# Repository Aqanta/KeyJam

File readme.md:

# Aqanta KeyJam

The Aqanta KeyJam is a powerful opensource macro-pad that can be configured to send HID keystrokes, run complex macros on a connected computer, or be used as a drum-pad. 
The KeyJam runs on an RP2040 (Pico) board and can use a companion Electron app for control.

All code, designs, and methodology can be found in this repo. The project is unfinished and will be updated over time.

## Drums on Alpine Linux

APK installs:

fluidsynth

fluidsynth python driver is here, needs to be installed manually

https://github.com/nwhitehead/pyfluidsynth

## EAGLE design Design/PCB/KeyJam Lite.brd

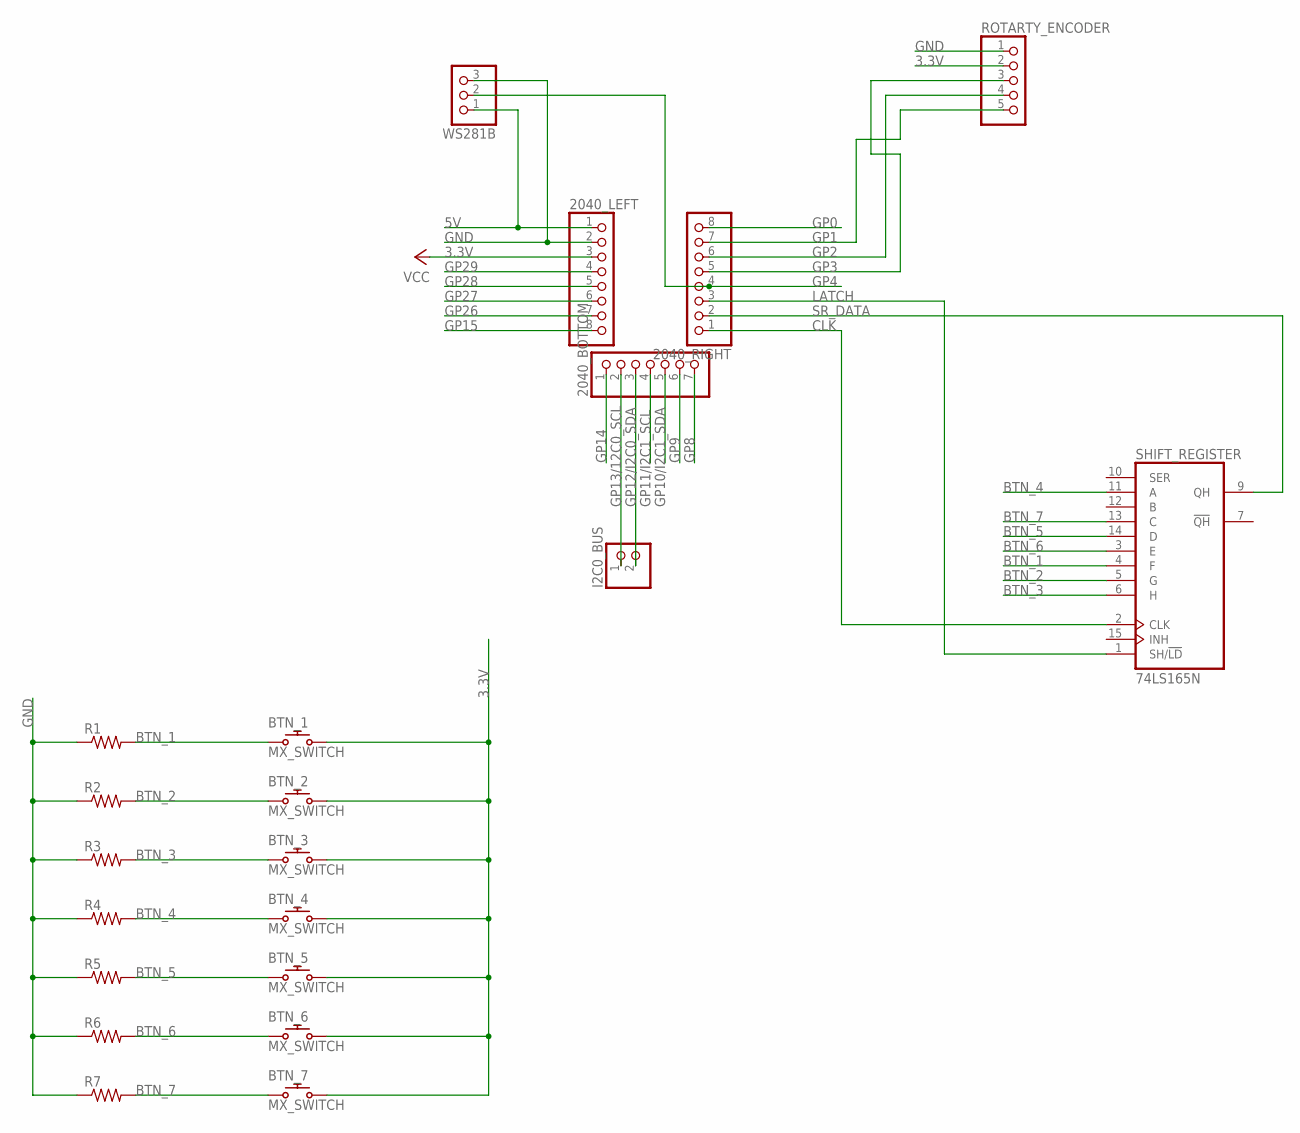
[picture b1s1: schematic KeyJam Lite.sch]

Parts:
2040_BOTTOM: PINHD-1X7; 1X07
2040_LEFT, 2040_RIGHT: PINHD-1X8; 1X08
BTN_1, BTN_2, BTN_3, BTN_4, BTN_5, BTN_6, BTN_7: MX_SWITCH
I2C0_BUS: PINHD-1X2; 1X02
R1, R2, R3, R4, R5, R6, R7: ADAFRUIT_R-US_R0805; ADAFRUIT_R0805
ROTARTY_ENCODER: PINHD-1X5; 1X05
SHIFT_REGISTER: 74LS165N; DIL16
WS281B: PINHD-1X3; 1X03

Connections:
3.3V: 2040_LEFT.3, BTN_1.S2 (2), BTN_2.S2 (2), BTN_3.S2 (2), BTN_4.S2 (2), BTN_5.S2 (2), BTN_6.S2 (2), BTN_7.S2 (2), ROTARTY_ENCODER.2, SHIFT_REGISTER.16 (VCC)
5V: 2040_LEFT.1, WS281B.1
BTN_1: BTN_1.S1 (1), R1.2, SHIFT_REGISTER.4 (F)
BTN_2: BTN_2.S1 (1), R2.2, SHIFT_REGISTER.5 (G)
BTN_3: BTN_3.S1 (1), R3.2, SHIFT_REGISTER.6 (H)
BTN_4: BTN_4.S1 (1), R4.2, SHIFT_REGISTER.11 (A)
BTN_5: BTN_5.S1 (1), R5.2, SHIFT_REGISTER.14 (D)
BTN_6: BTN_6.S1 (1), R6.2, SHIFT_REGISTER.3 (E)
BTN_7: BTN_7.S1 (1), R7.2, SHIFT_REGISTER.13 (C)
CLK: 2040_RIGHT.1, SHIFT_REGISTER.2 (CLK)
GND: 2040_LEFT.2, R1.1, R2.1, R3.1, R4.1, R5.1, R6.1, R7.1, ROTARTY_ENCODER.1, SHIFT_REGISTER.8 (GND), WS281B.3
GP0: 2040_RIGHT.8
GP1: 2040_RIGHT.7, ROTARTY_ENCODER.5
GP2: 2040_RIGHT.6, ROTARTY_ENCODER.4
GP3: 2040_RIGHT.5, ROTARTY_ENCODER.3
GP4: 2040_RIGHT.4, WS281B.2
GP8: 2040_BOTTOM.7
GP9: 2040_BOTTOM.6
GP10/I2C1_SDA: 2040_BOTTOM.5
GP11/I2C1_SCL: 2040_BOTTOM.4
GP12/I2C0_SDA: 2040_BOTTOM.3, I2C0_BUS.2
GP13/12C0_SCL: 2040_BOTTOM.2, I2C0_BUS.1
GP14: 2040_BOTTOM.1
GP15: 2040_LEFT.8
GP26: 2040_LEFT.7
GP27: 2040_LEFT.6
GP28: 2040_LEFT.5
GP29: 2040_LEFT.4
LATCH: 2040_RIGHT.3, SHIFT_REGISTER.1 (SH/!LD)
SR_DATA: 2040_RIGHT.2, SHIFT_REGISTER.9 (QH)

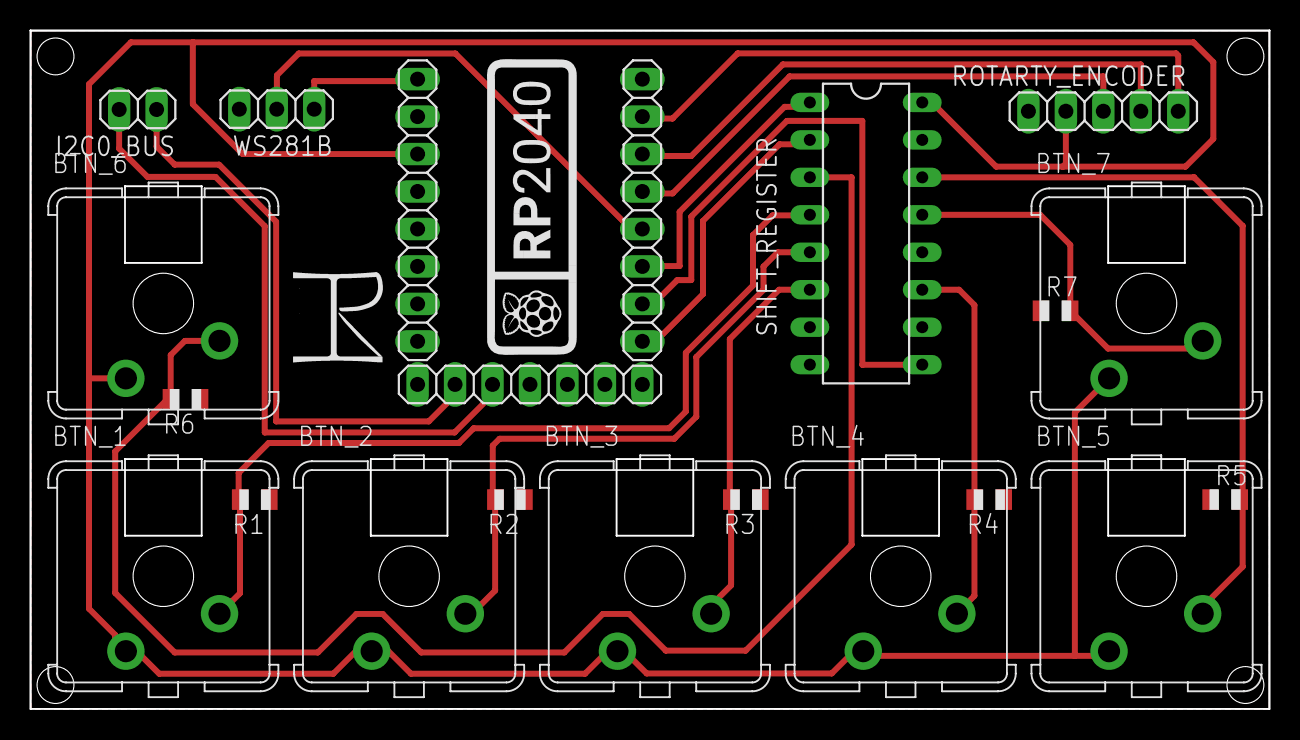
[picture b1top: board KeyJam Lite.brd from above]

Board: 2 copper layers, 84.0 x 46.0 mm, 22 parts (0 on the bottom side), 19 nets.

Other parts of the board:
U$1: RASPI_RP2040_LOGO_20MM

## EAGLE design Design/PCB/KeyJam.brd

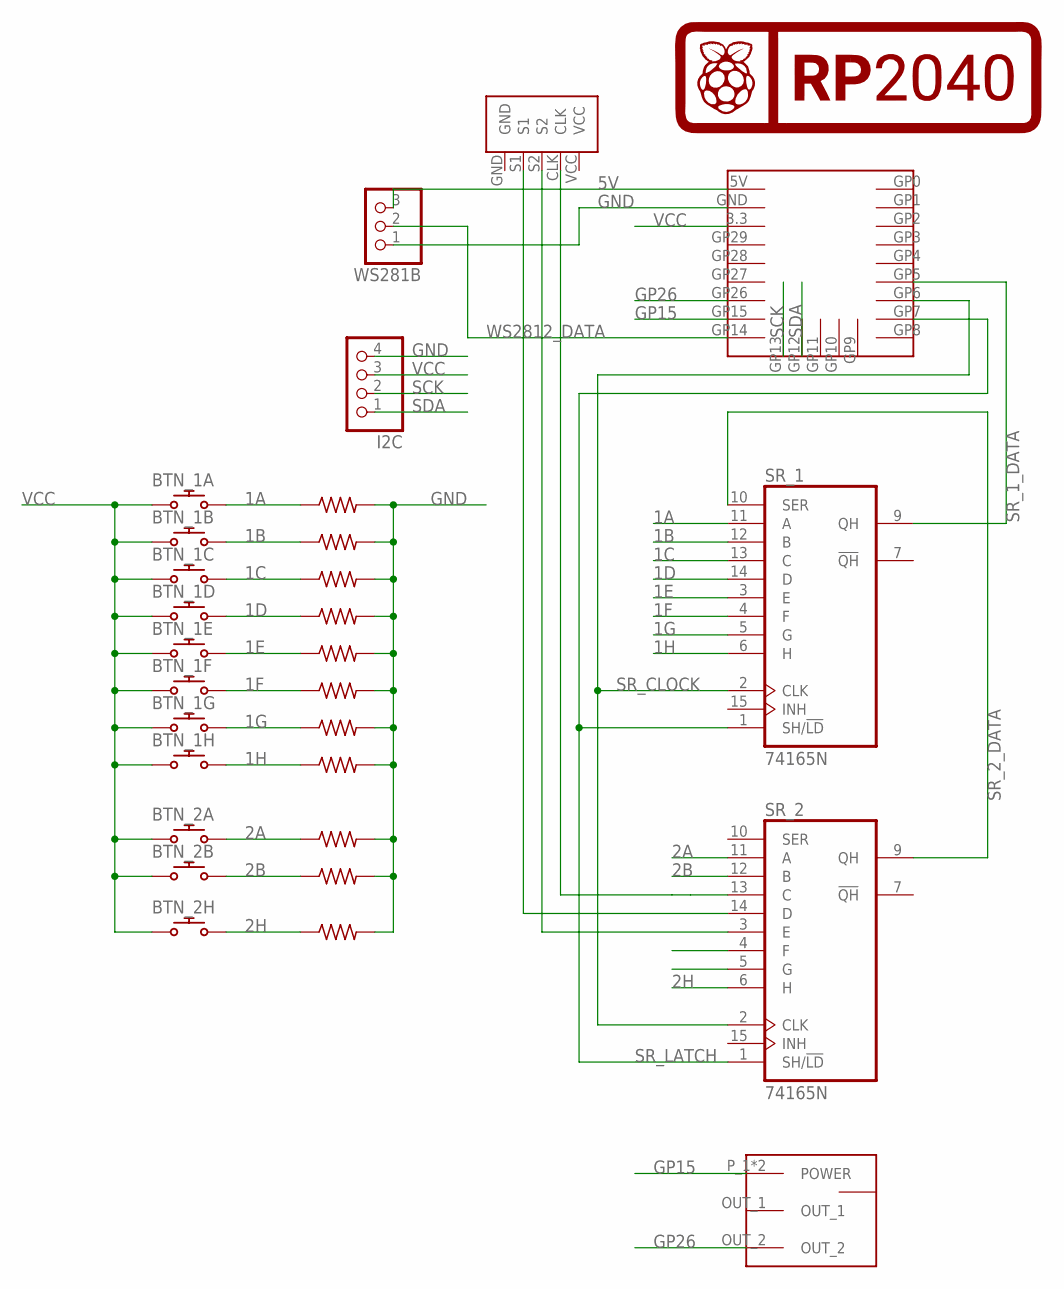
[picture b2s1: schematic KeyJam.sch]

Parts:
BTN_1A, BTN_1B, BTN_1C, BTN_1D, BTN_1E, BTN_1F, BTN_1G, BTN_1H, BTN_2A, BTN_2B, BTN_2H: MX_SWITCH
I2C: PINHD-1X4; 1X04
R1, R2, R3, R4, R5, R6, R7, R8, R9, R10, R11: R-US_R1206; R1206
SLIDER: SLIDER
SR_1, SR_2: 74165N; DIL16
U$1: RP2040-ZERO
U$2: ROUND_ROTARY
U$3: RASPI_RP2040_LOGO_20MM
WS281B: PINHD-1X3; 1X03

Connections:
1A: BTN_1A.$2 (2), R1.1, SR_1.11 (A)
1B: BTN_1B.$2 (2), R2.1, SR_1.12 (B)
1C: BTN_1C.$2 (2), R3.1, SR_1.13 (C)
1D: BTN_1D.$2 (2), R4.1, SR_1.14 (D)
1E: BTN_1E.$2 (2), R5.1, SR_1.3 (E)
1F: BTN_1F.$2 (2), R6.1, SR_1.4 (F)
1G: BTN_1G.$2 (2), R7.1, SR_1.5 (G)
1H: BTN_1H.$2 (2), R8.1, SR_1.6 (H)
2A: BTN_2A.$2 (2), R9.1, SR_2.11 (A)
2B: BTN_2B.$2 (2), R10.1, SR_2.12 (B)
2H: BTN_2H.$2 (2), R11.1, SR_2.6 (H)
5V: U$1.5V (5), WS281B.3
GND: I2C.4, R1.2, R2.2, R3.2, R4.2, R5.2, R6.2, R7.2, R8.2, R9.2, R10.2, R11.2, SLIDER.GND_1 (GND), SLIDER.GND_2 (GND), SR_1.8 (GND), SR_2.8 (GND), U$1.GND, U$2.GND, WS281B.1
GP15: SLIDER.P_1 (POWER), SLIDER.P_2 (POWER), U$1.GP15
GP26: SLIDER.OUT_2, U$1.GP26
unnamed: SR_2.13 (C), U$2.CLK
unnamed: SR_2.14 (D), U$2.S1
unnamed: SR_2.3 (E), U$2.S2
SCK: I2C.2, U$1.GP13
SDA: I2C.1, U$1.GP12
SR_1_DATA: SR_1.9 (QH), U$1.GP5
SR_2_DATA: SR_1.10 (SER), SR_2.9 (QH)
SR_CLOCK: SR_1.2 (CLK), SR_2.2 (CLK), U$1.GP6
SR_LATCH: SR_1.1 (SH/!LD), SR_2.1 (SH/!LD), U$1.GP7
VCC: BTN_1A.$1 (1), BTN_1B.$1 (1), BTN_1C.$1 (1), BTN_1D.$1 (1), BTN_1E.$1 (1), BTN_1F.$1 (1), BTN_1G.$1 (1), BTN_1H.$1 (1), BTN_2A.$1 (1), BTN_2B.$1 (1), BTN_2H.$1 (1), I2C.3, SR_1.16 (VCC), SR_2.16 (VCC), U$1.3.3, U$2.VCC
WS2812_DATA: U$1.GP14, WS281B.2

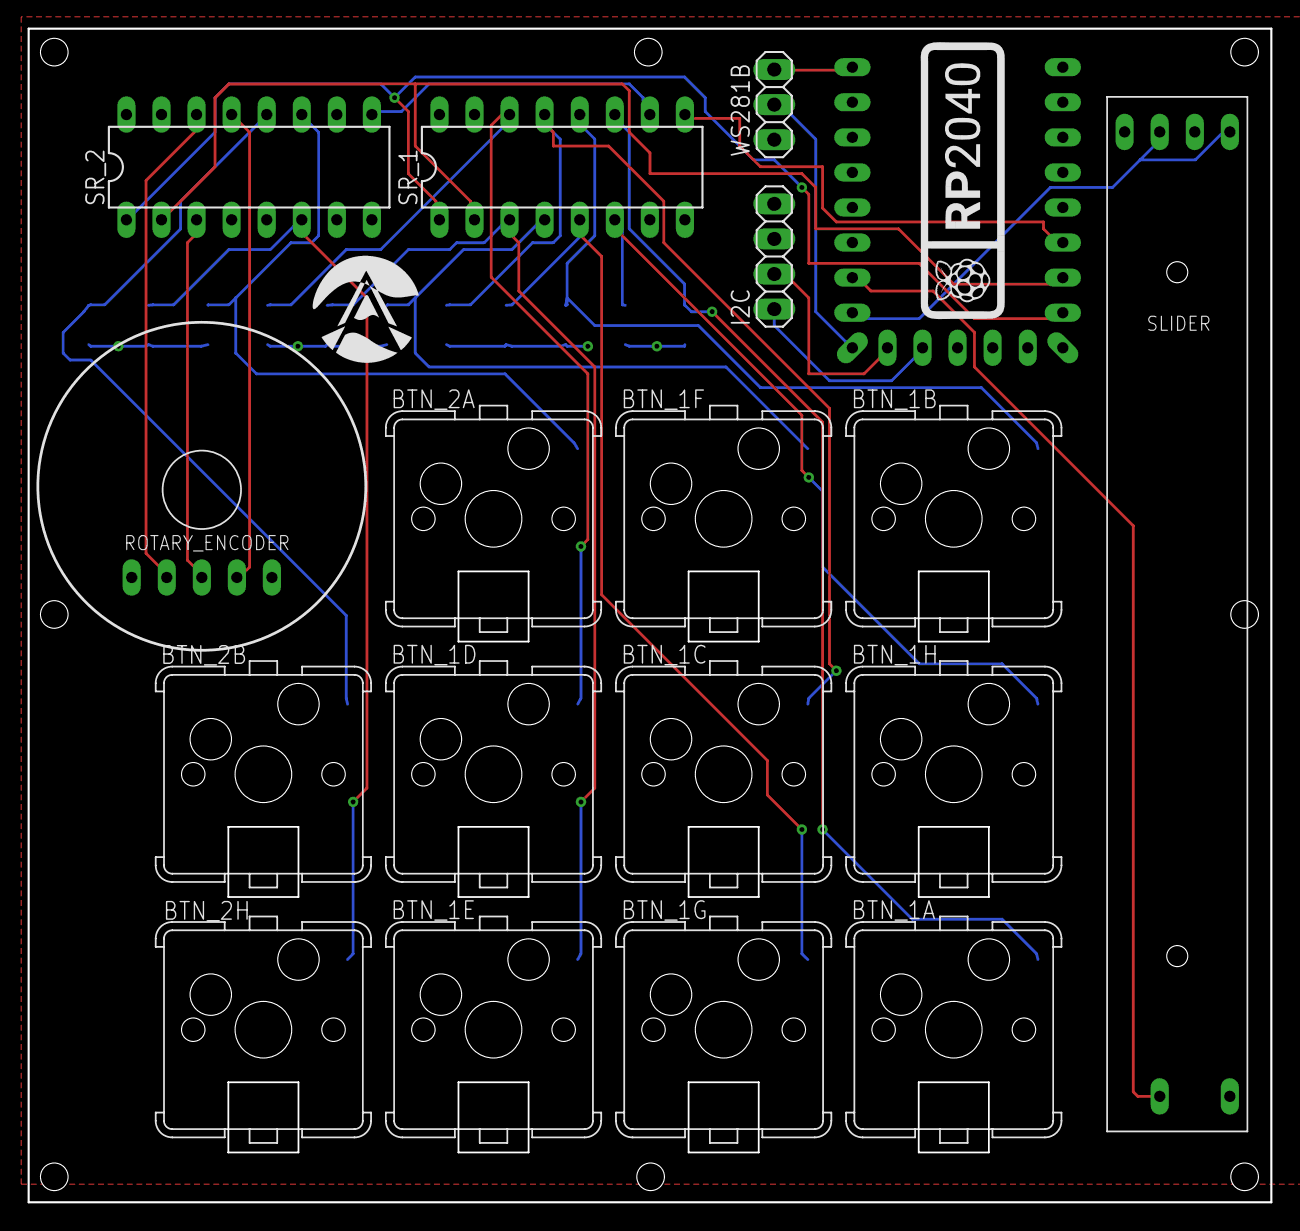
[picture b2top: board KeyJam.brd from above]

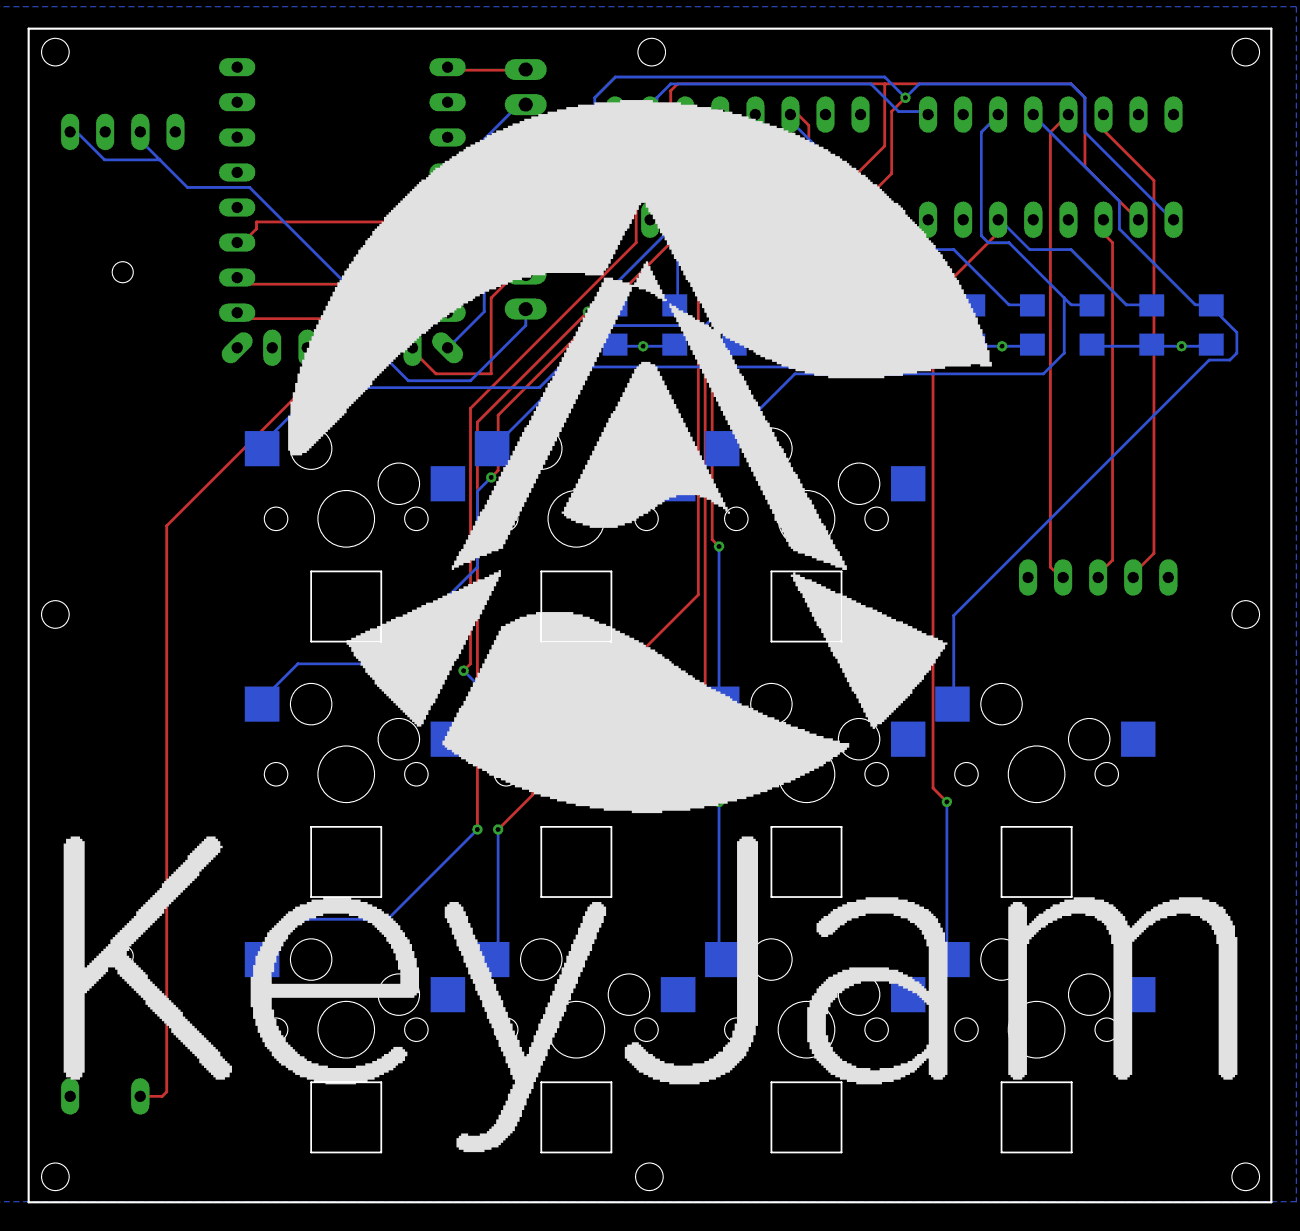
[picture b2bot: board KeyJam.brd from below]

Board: 2 copper layers, 90.0 x 85.0 mm, 30 parts (11 on the bottom side), 26 nets.

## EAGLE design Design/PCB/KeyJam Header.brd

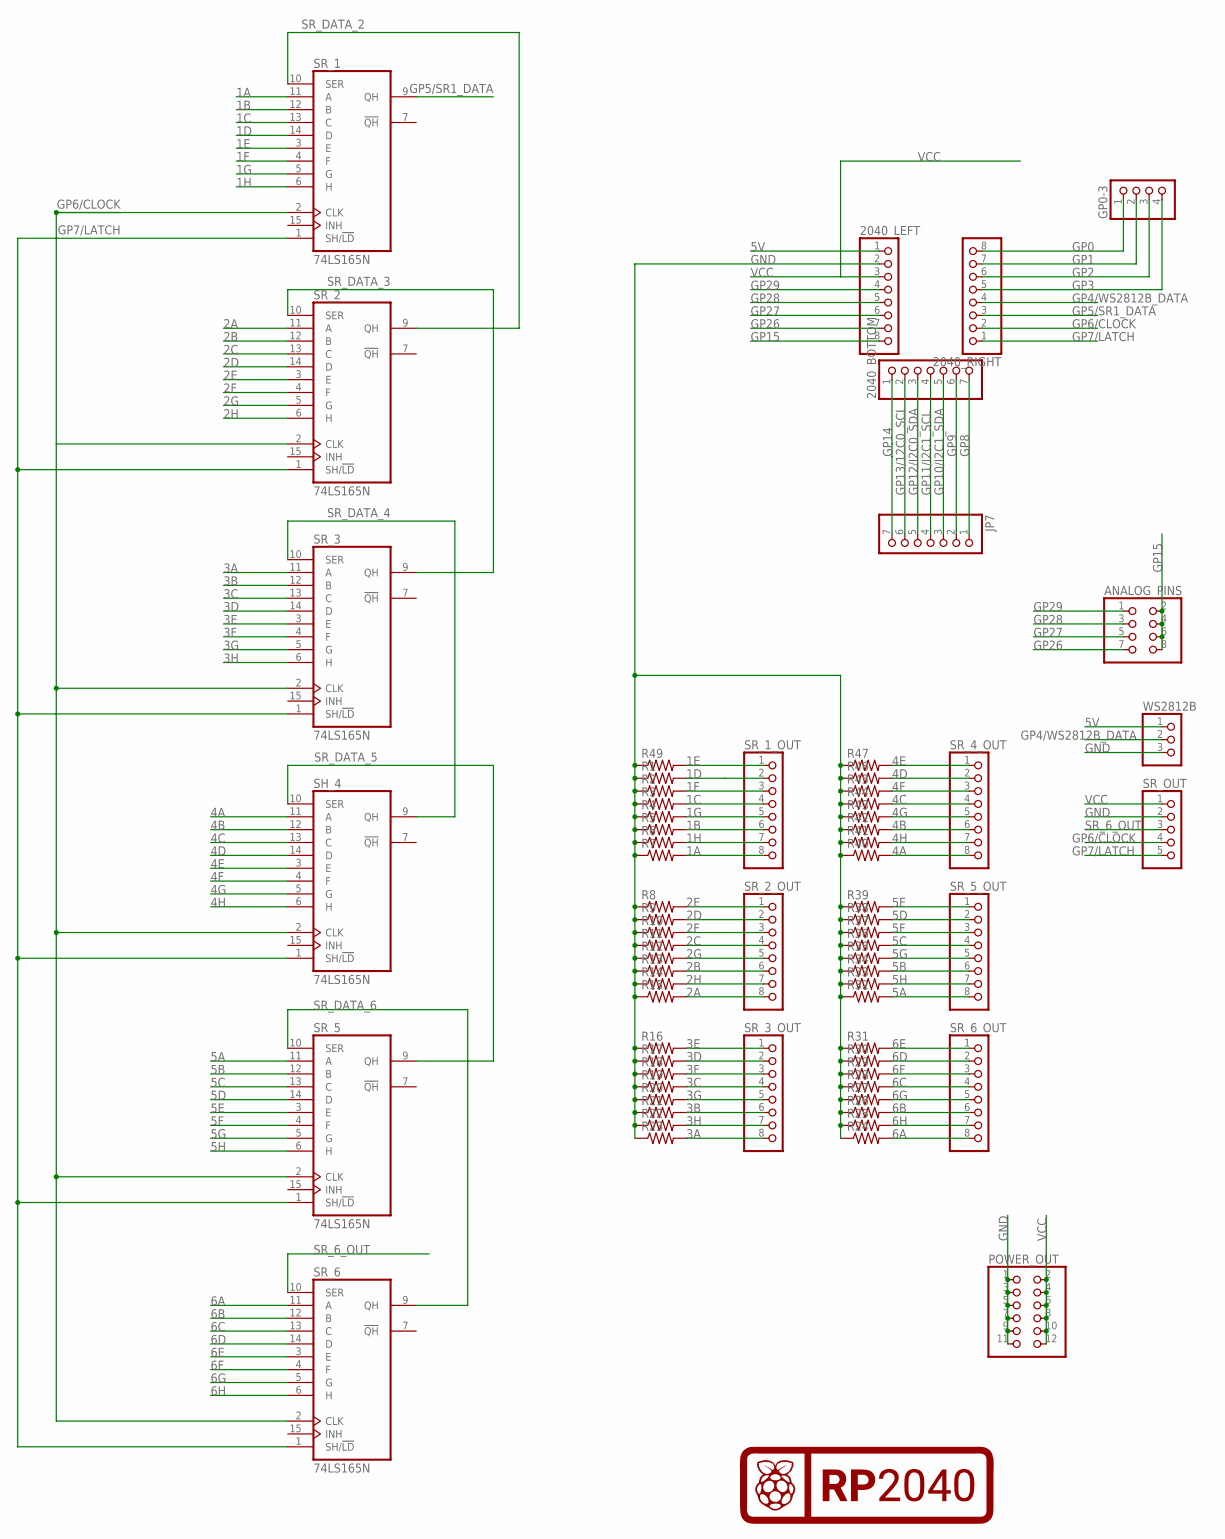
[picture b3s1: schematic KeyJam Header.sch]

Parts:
2040_BOTTOM: PINHD-1X7; 1X07
2040_LEFT, 2040_RIGHT: PINHD-1X8; 1X08
ANALOG_PINS: PINHD-2X4; 2X04
GP0-3: PINHD-1X4; 1X04
JP7: PINHD-1X7; 1X07
POWER_OUT: PINHD-2X6; 2X06
R1, R2, R3, R4, R5, R6, R7, R8, R9, R10, R11, R12, R13, R14, R15, R16, R17, R18, R19, R20, R21, R22, R23, R24, R25, R26, R27, R28, R29, R30, R31, R32, R33, R34, R35, R36, R37, R38, R39, R40, R41, R42, R43, R44, R45, R46, R47, R49: R-US_R1206; R1206
SH_4: 74LS165N; DIL16
SR_1, SR_2, SR_3, SR_5, SR_6: 74LS165N; DIL16
SR_1_OUT, SR_2_OUT, SR_3_OUT, SR_4_OUT, SR_5_OUT, SR_6_OUT: PINHD-1X8; 1X08
SR_OUT: PINHD-1X5; 1X05
U$1: RASPI_RP2040_LOGO_20MM
WS2812B: PINHD-1X3; 1X03

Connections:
1A: R7.2, SR_1.11 (A), SR_1_OUT.8
1B: R5.2, SR_1.12 (B), SR_1_OUT.6
1C: R3.2, SR_1.13 (C), SR_1_OUT.4
1D: R1.2, SR_1.14 (D), SR_1_OUT.2
1E: R49.2, SR_1.3 (E), SR_1_OUT.1
1F: R2.2, SR_1.4 (F), SR_1_OUT.3
1G: R4.2, SR_1.5 (G), SR_1_OUT.5
1H: R6.2, SR_1.6 (H), SR_1_OUT.7
2A: R15.2, SR_2.11 (A), SR_2_OUT.8
2B: R13.2, SR_2.12 (B), SR_2_OUT.6
2C: R11.2, SR_2.13 (C), SR_2_OUT.4
2D: R9.2, SR_2.14 (D), SR_2_OUT.2
2E: R8.2, SR_2.3 (E), SR_2_OUT.1
2F: R10.2, SR_2.4 (F), SR_2_OUT.3
2G: R12.2, SR_2.5 (G), SR_2_OUT.5
2H: R14.2, SR_2.6 (H), SR_2_OUT.7
3A: R23.2, SR_3.11 (A), SR_3_OUT.8
3B: R21.2, SR_3.12 (B), SR_3_OUT.6
3C: R19.2, SR_3.13 (C), SR_3_OUT.4
3D: R17.2, SR_3.14 (D), SR_3_OUT.2
3E: R16.2, SR_3.3 (E), SR_3_OUT.1
3F: R18.2, SR_3.4 (F), SR_3_OUT.3
3G: R20.2, SR_3.5 (G), SR_3_OUT.5
3H: R22.2, SR_3.6 (H), SR_3_OUT.7
4A: R40.2, SH_4.11 (A), SR_4_OUT.8
4B: R42.2, SH_4.12 (B), SR_4_OUT.6
4C: R44.2, SH_4.13 (C), SR_4_OUT.4
4D: R46.2, SH_4.14 (D), SR_4_OUT.2
4E: R47.2, SH_4.3 (E), SR_4_OUT.1
4F: R45.2, SH_4.4 (F), SR_4_OUT.3
4G: R43.2, SH_4.5 (G), SR_4_OUT.5
4H: R41.2, SH_4.6 (H), SR_4_OUT.7
5A: R32.2, SR_5.11 (A), SR_5_OUT.8
5B: R34.2, SR_5.12 (B), SR_5_OUT.6
5C: R36.2, SR_5.13 (C), SR_5_OUT.4
5D: R38.2, SR_5.14 (D), SR_5_OUT.2
5E: R39.2, SR_5.3 (E), SR_5_OUT.1
5F: R37.2, SR_5.4 (F), SR_5_OUT.3
5G: R35.2, SR_5.5 (G), SR_5_OUT.5
5H: R33.2, SR_5.6 (H), SR_5_OUT.7
5V: 2040_LEFT.1, WS2812B.1
6A: R24.2, SR_6.11 (A), SR_6_OUT.8
6B: R26.2, SR_6.12 (B), SR_6_OUT.6
6C: R28.2, SR_6.13 (C), SR_6_OUT.4
6D: R30.2, SR_6.14 (D), SR_6_OUT.2
6E: R31.2, SR_6.3 (E), SR_6_OUT.1
6F: R29.2, SR_6.4 (F), SR_6_OUT.3
6G: R27.2, SR_6.5 (G), SR_6_OUT.5
6H: R25.2, SR_6.6 (H), SR_6_OUT.7
GND: 2040_LEFT.2, POWER_OUT.1, POWER_OUT.3, POWER_OUT.5, POWER_OUT.7, POWER_OUT.9, POWER_OUT.11, R1.1, R2.1, R3.1, R4.1, R5.1, R6.1, R7.1, R8.1, R9.1, R10.1, R11.1, R12.1, R13.1, R14.1, R15.1, R16.1, R17.1, R18.1, R19.1, R20.1, R21.1, R22.1, R23.1, R24.1, R25.1, R26.1, R27.1, R28.1, R29.1, R30.1, R31.1, R32.1, R33.1, R34.1, R35.1, R36.1, R37.1, R38.1, R39.1, R40.1, R41.1, R42.1, R43.1, R44.1, R45.1, R46.1, R47.1, R49.1, SH_4.8 (GND), SR_1.8 (GND), SR_2.8 (GND), SR_3.8 (GND), SR_5.8 (GND), SR_6.8 (GND), SR_OUT.2, WS2812B.3
GP0: 2040_RIGHT.8, GP0-3.1
GP1: 2040_RIGHT.7, GP0-3.2
GP2: 2040_RIGHT.6, GP0-3.3
GP3: 2040_RIGHT.5, GP0-3.4
GP4/WS2812B_DATA: 2040_RIGHT.4, WS2812B.2
GP5/SR1_DATA: 2040_RIGHT.3, SR_1.9 (QH)
GP6/CLOCK: 2040_RIGHT.2, SH_4.2 (CLK), SR_1.2 (CLK), SR_2.2 (CLK), SR_3.2 (CLK), SR_5.2 (CLK), SR_6.2 (CLK), SR_OUT.4
GP7/LATCH: 2040_RIGHT.1, SH_4.1 (SH/!LD), SR_1.1 (SH/!LD), SR_2.1 (SH/!LD), SR_3.1 (SH/!LD), SR_5.1 (SH/!LD), SR_6.1 (SH/!LD), SR_OUT.5
GP8: 2040_BOTTOM.7, JP7.1
GP9: 2040_BOTTOM.6, JP7.2
GP10/I2C1_SDA: 2040_BOTTOM.5, JP7.3
GP11/I2C1_SCL: 2040_BOTTOM.4, JP7.4
GP12/I2C0_SDA: 2040_BOTTOM.3, JP7.5
GP13/12C0_SCL: 2040_BOTTOM.2, JP7.6
GP14: 2040_BOTTOM.1, JP7.7
GP15: 2040_LEFT.8, ANALOG_PINS.2, ANALOG_PINS.4, ANALOG_PINS.6, ANALOG_PINS.8
GP26: 2040_LEFT.7, ANALOG_PINS.7
GP27: 2040_LEFT.6, ANALOG_PINS.5
GP28: 2040_LEFT.5, ANALOG_PINS.3
GP29: 2040_LEFT.4, ANALOG_PINS.1
SR_6_OUT: SR_6.10 (SER), SR_OUT.3
SR_DATA_2: SR_1.10 (SER), SR_2.9 (QH)
SR_DATA_3: SR_2.10 (SER), SR_3.9 (QH)
SR_DATA_4: SH_4.9 (QH), SR_3.10 (SER)
SR_DATA_5: SH_4.10 (SER), SR_5.9 (QH)
SR_DATA_6: SR_5.10 (SER), SR_6.9 (QH)
VCC: 2040_LEFT.3, POWER_OUT.2, POWER_OUT.4, POWER_OUT.6, POWER_OUT.8, POWER_OUT.10, POWER_OUT.12, SH_4.16 (VCC), SR_1.16 (VCC), SR_2.16 (VCC), SR_3.16 (VCC), SR_5.16 (VCC), SR_6.16 (VCC), SR_OUT.1

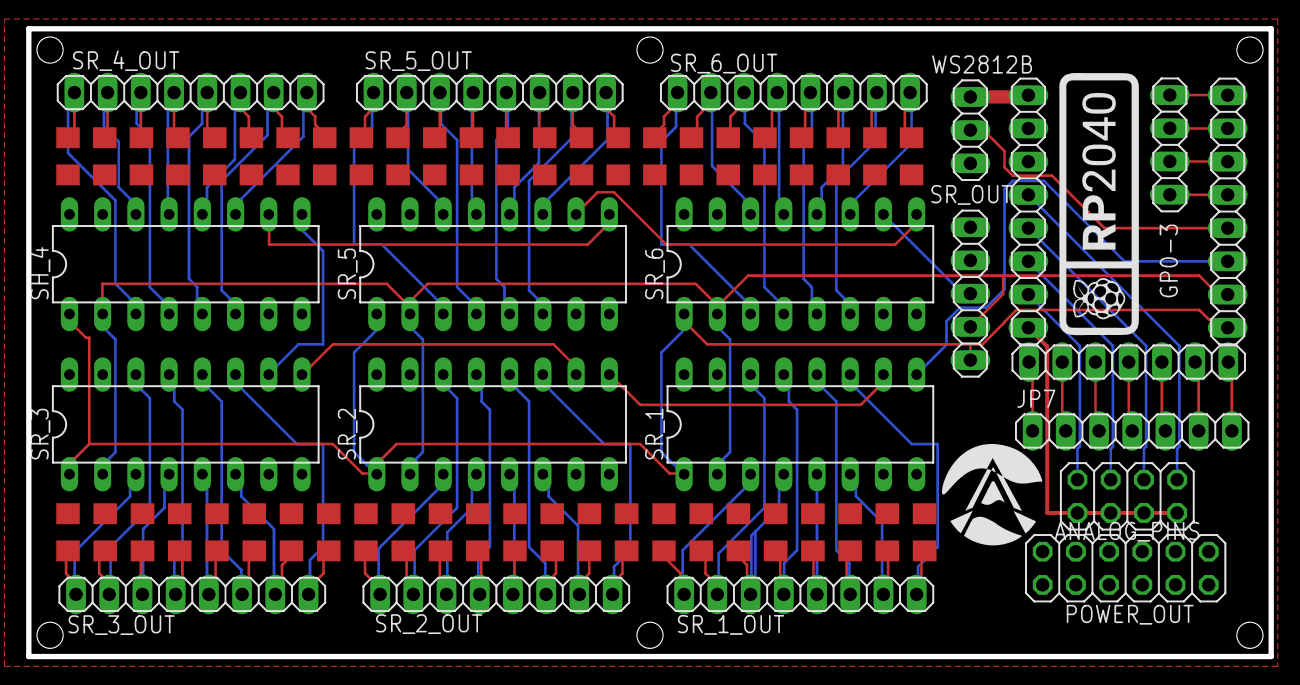
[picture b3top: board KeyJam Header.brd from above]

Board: 2 copper layers, 95.0 x 48.0 mm, 70 parts (0 on the bottom side), 77 nets.

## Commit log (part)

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2024-02-24 Added Prototype Designs
2024-02-24 Basic Control App
2024-02-24 Initial firmware commit
2024-02-24 Removed accidental libary
2024-02-27 Basic app to KeyJam communication
2024-02-27 Updated keycaps
2024-02-27 Added support for consumer keys
2024-02-27 Key map changes persist
2024-02-27 Added Bulma SASS support
2024-03-08 added the funnies
2024-03-09 Added PCB layouts
2024-03-09 Added various 3D Files
    Not all designs are final
2024-03-09 Added button layout mapping
2024-03-09 Added basic volume code
2024-03-09 Updated readme(s)
2024-03-10 v2 of KeyJam frame
2024-03-14 Added macros and rotary encoders
2024-03-14 Latest design changes
2024-03-17 Added slider
2024-03-17 Updated frame design
    More space for the rotary encoder and slider knob. Increased size of USB port.
2024-03-17 Made text cutout thicker
2024-04-04 Updated KeyJam Max Files
2024-04-04 Added auto-connect, app packaging, & disconnect recognition
2024-04-04 Fixed path location of config file

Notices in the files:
parts and their libraries:
SparkFun-Aesthetics: Licensing: Creative Commons ShareAlike 4.0 International - https://creativecommons.org/licenses/by-sa/4.0
